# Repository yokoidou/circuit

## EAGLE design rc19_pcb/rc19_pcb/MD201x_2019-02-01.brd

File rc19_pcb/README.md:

rc19_pcb.zipには，3組の回路図・基板データファイル，合計6つのファイルが含まれます．
MD201x_2018-11-25.sch/brdは1次審査まで使用したモータドライバで，ファームウェアはここ(https://github.com/yskhara/md201x) に置いてあります．
MD201x_2019-02-01.sch/brdは1次審査以降に使用したモータドライバで，ファームウェアはここ(https://github.com/yskhara/mdpos201x) に置いてあります．
usbcan_20190426.sch/brdは2次落ち以降に発注したUSB-CAN基板です．ファームウェアはまだありませんし，基板もテストできていませんが，参考程度に添付しておきます．

Follow me on:
GitHub: https://github.com/yskhara

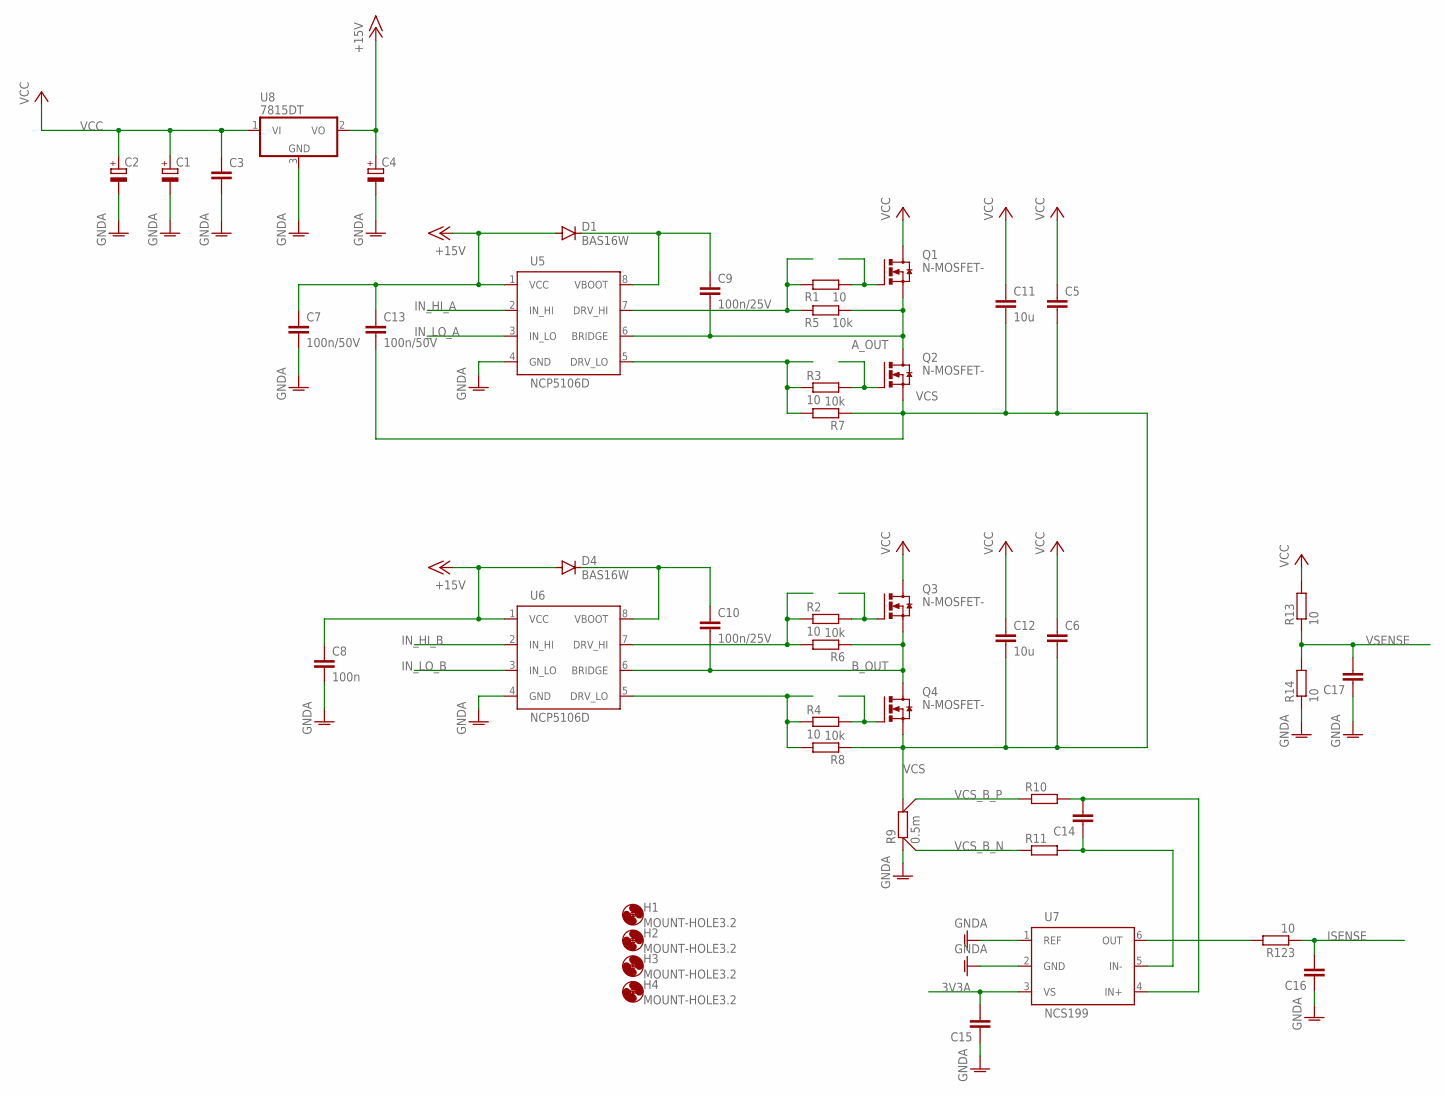
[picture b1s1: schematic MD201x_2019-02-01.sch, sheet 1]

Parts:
C1, C2: CPOL-EUE5-10.5; E5-10,5
C3, C5, C6, C14, C15, C16, C17: C-EUC0603; C0603
C4: CPOL-EUE2.5-5; E2,5-5
C7, C13: 100n/50V; C0603
C8: 100n; C0603
C9, C10: 100n/25V; C0603
C11, C12: 10u; C1210
D1, D4: BAS16W; SOD323-R
H1, H2, H3, H4: MOUNT-HOLE3.2; 3,2
Q1, Q2, Q3, Q4: N-MOSFET-; SOT669
R1, R2, R3, R4, R13, R14, R123: 10; R0603
R5, R6, R7, R8: 10k; R0603
R9: 0.5m; CSS2H-2512
R10, R11: R-EU_R0603; R0603
U5, U6: NCP5106D; SOIC127P600X175-8
U7: NCS199; SOT65P210X110-6
U8: 7815DT; TO252

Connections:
3V3A: C15.2, U7.3 (VS); also elsewhere on the board
+15V: C4.+, C7.1, C8.1, C13.1, D1.A, D4.A, U5.1 (VCC), U6.1 (VCC), U8.2 (VO); also elsewhere on the board
A_OUT: C9.2, Q1.1 (SOURCE), Q1.2 (SOURCE), Q1.3 (SOURCE), Q2.5 (DRAIN), R5.1, U5.6 (BRIDGE)
B_OUT: C10.2, Q3.1 (SOURCE), Q3.2 (SOURCE), Q3.3 (SOURCE), Q4.5 (DRAIN), R6.1, U6.6 (BRIDGE)
GNDA: C1.-, C2.-, C3.2, C4.-, C7.2, C8.2, C15.1, C16.1, C17.1, R9.1$1 (1), R9.1$2 (1), R14.1, U5.4 (GND), U6.4 (GND), U7.1 (REF), U7.2 (GND), U8.3 (GND); also elsewhere on the board
IN_HI_A: U5.2 (IN_HI); also elsewhere on the board
IN_HI_B: U6.2 (IN_HI); also elsewhere on the board
IN_LO_A: U5.3 (IN_LO); also elsewhere on the board
IN_LO_B: U6.3 (IN_LO); also elsewhere on the board
ISENSE: C16.2, R123.1; also elsewhere on the board
unnamed: R1.1, R5.2, U5.7 (DRV_HI)
unnamed: R2.1, R6.2, U6.7 (DRV_HI)
unnamed: Q1.4 (GATE), R1.2
unnamed: R4.1, R8.2, U6.5 (DRV_LO)
unnamed: R123.2, U7.6 (OUT)
unnamed: R3.1, R7.2, U5.5 (DRV_LO)
unnamed: Q3.4 (GATE), R2.2
unnamed: C14.2, R10.2, U7.4 (IN+)
unnamed: C14.1, R11.2, U7.5 (IN-)
unnamed: Q2.4 (GATE), R3.2
unnamed: Q4.4 (GATE), R4.2
unnamed: C10.1, D4.C, U6.8 (VBOOT)
unnamed: C9.1, D1.C, U5.8 (VBOOT)
VCC: C1.+, C2.+, C3.1, C5.1, C6.1, C11.1, C12.1, Q1.5 (DRAIN), Q3.5 (DRAIN), R13.2, U8.1 (VI)
VCS: C5.2, C6.2, C11.2, C12.2, C13.2, Q2.1 (SOURCE), Q2.2 (SOURCE), Q2.3 (SOURCE), Q4.1 (SOURCE), Q4.2 (SOURCE), Q4.3 (SOURCE), R7.1, R8.1, R9.2$1 (2), R9.2$2 (2)
VCS_B_N: R9.1S, R11.1
VCS_B_P: R9.2S, R10.1
VSENSE: C17.2, R13.1, R14.2; also elsewhere on the board

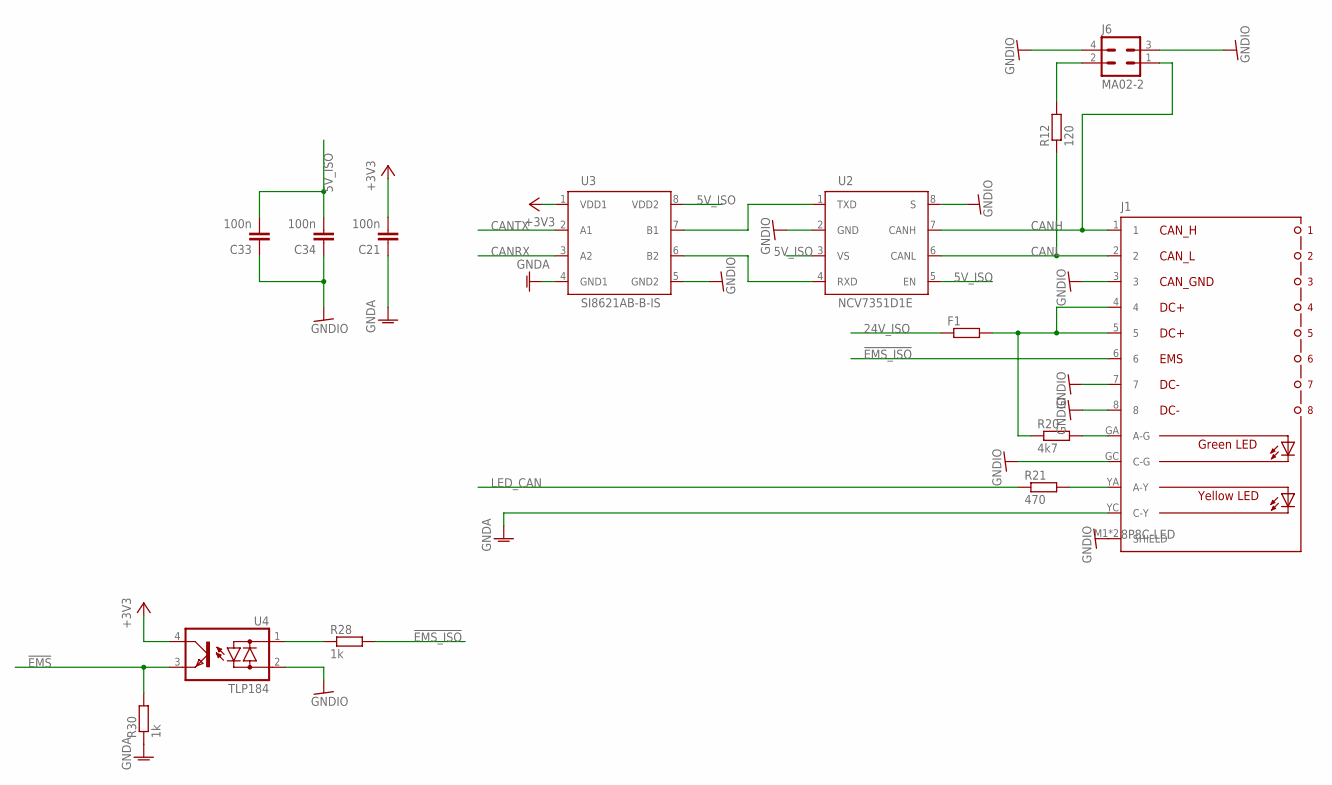
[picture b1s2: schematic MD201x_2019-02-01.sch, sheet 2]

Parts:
C21, C34: 100n; C0603
C33: 100n; C0805
F1: R-EU_R1206; R1206
J1: 8P8C-LED
J6: MA02-2; MA02-2W
R12: 120; R0603
R20: 4k7; R0603
R21: 470; R0603
R28, R30: 1k; R0603
U2: NCV7351D1E; SO08
U3: SI8621AB-B-IS; SO08
U4: TLP184; 11-4M1S

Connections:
5V_ISO: C33.2, C34.2, U2.3 (VS), U2.5 (EN), U3.8 (VDD2); also elsewhere on the board
24V_ISO: F1.1; also elsewhere on the board
!EMS: R30.2, U4.3 (E); also elsewhere on the board
!EMS_ISO: J1.6, R28.2
+3V3: C21.2, U3.1 (VDD1), U4.4 (C); also elsewhere on the board
CANH: J1.1, J6.1, U2.7 (CANH)
CANL: J1.2, R12.1, U2.6 (CANL)
CANRX: U3.3 (A2); also elsewhere on the board
CANTX: U3.2 (A1); also elsewhere on the board
GNDA: C21.1, J1.YC (C-Y), R30.1, U3.4 (GND1); also elsewhere on the board
GNDIO: C33.1, C34.1, J1.3, J1.7, J1.8, J1.GC (C-G), J1.M1 (SHIELD), J1.M2 (SHIELD), J6.3, J6.4, U2.2 (GND), U2.8 (S), U3.5 (GND2), U4.2 (AC2); also elsewhere on the board
LED_CAN: R21.1; also elsewhere on the board
unnamed: F1.2, J1.4, J1.5, R20.1
unnamed: J6.2, R12.2
unnamed: J1.GA (A-G), R20.2
unnamed: J1.YA (A-Y), R21.2
unnamed: U2.1 (TXD), U3.7 (B1)
unnamed: U2.4 (RXD), U3.6 (B2)
unnamed: R28.1, U4.1 (AC1)

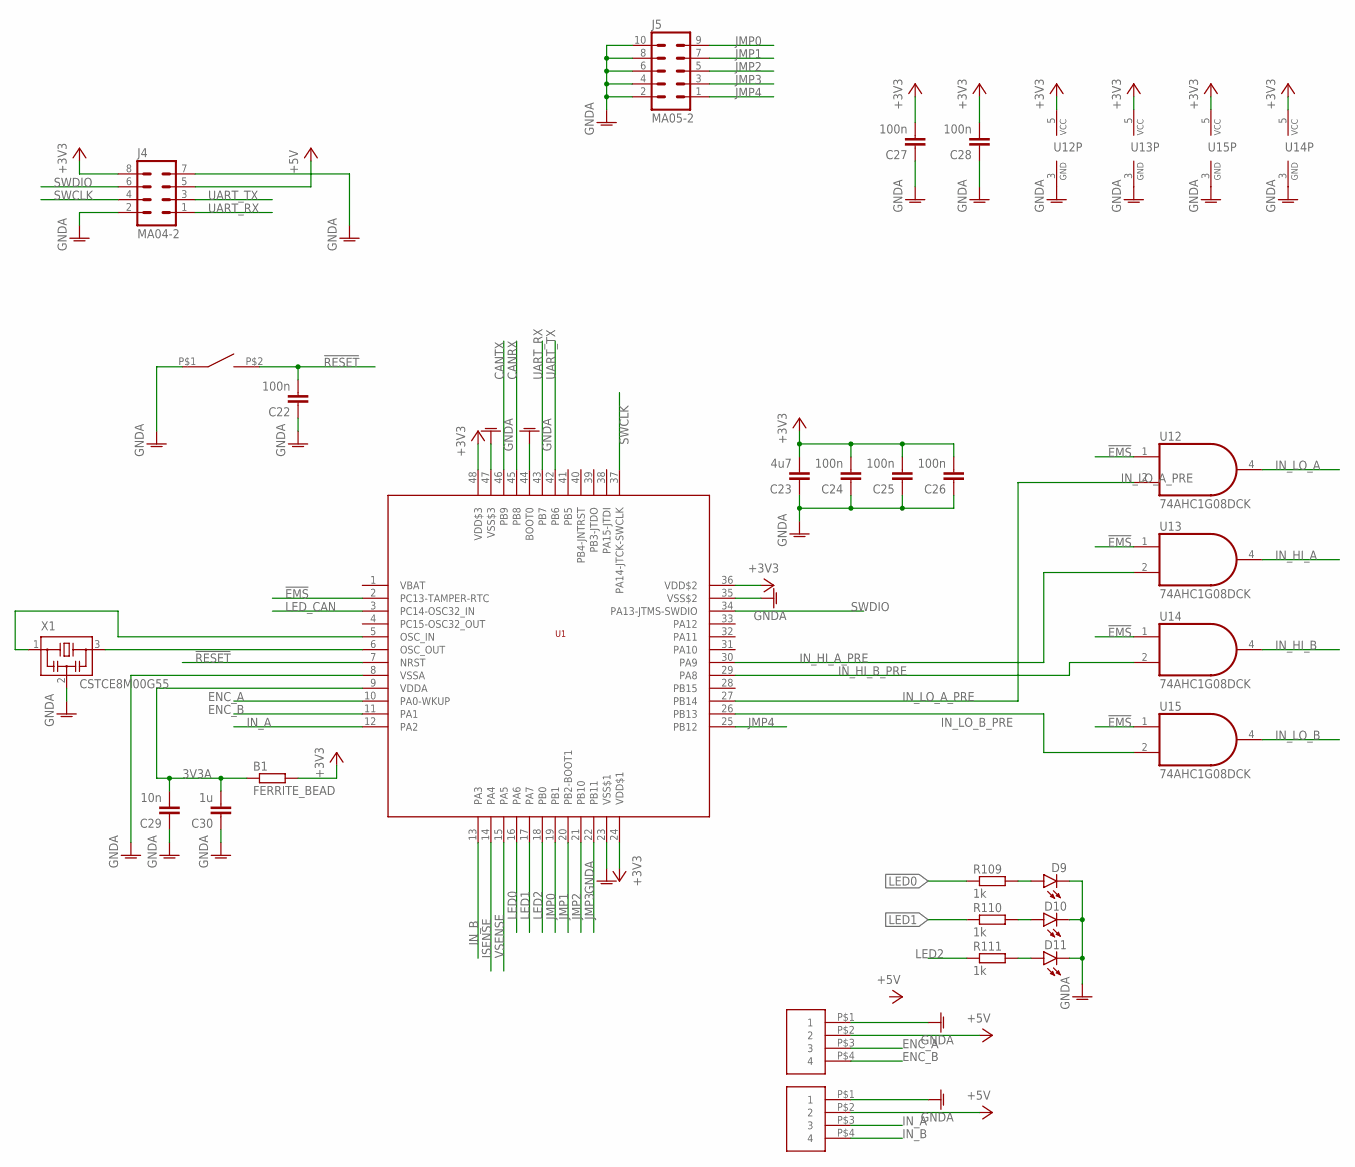
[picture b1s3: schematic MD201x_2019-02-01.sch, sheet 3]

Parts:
B1: FERRITE_BEAD; R0603
C22, C24, C25, C26, C27, C28: 100n; C0603
C23: 4u7; C0805
C29: 10n; C0603
C30: 1u; C0603
D9, D10, D11: LEDCHIPLED_0805; CHIPLED_0805
J2, J3: XH-4-SIDE; CON-XH-4-SIDE
J4: MA04-2; MA04-2W
J5: MA05-2; MA05-2W
R109, R110, R111: 1k; R0603
S1: SWITCH_TACTILETOP; SWITCH_TACTILE_3X6
U1: STM32F103C8; LQFP48
U12, U13, U14, U15: 74AHC1G08DCK; SC70-5
X1: CSTCE8M00G55

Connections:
3V3A: B1.1, C29.2, C30.2, U1.9 (VDDA); also elsewhere on the board
!EMS: U1.2 (PC13-TAMPER-RTC), U12.1 (I0), U13.1 (I0), U14.1 (I0), U15.1 (I0); also elsewhere on the board
!RESET: C22.2, S1.P$2 (2), U1.7 (NRST)
+3V3: B1.2, C23.2, C24.2, C25.2, C26.2, C27.2, C28.2, J4.8, U1.24 (VDD$1), U1.36 (VDD$2), U1.48 (VDD$3), U12.5 (VCC), U13.5 (VCC), U14.5 (VCC), U15.5 (VCC); also elsewhere on the board
+5V: J2.P$2 (2), J3.P$2 (2), J4.5; also elsewhere on the board
CANRX: U1.45 (PB8); also elsewhere on the board
CANTX: U1.46 (PB9); also elsewhere on the board
ENC_A: J2.P$3 (3), U1.10 (PA0-WKUP)
ENC_B: J2.P$4 (4), U1.11 (PA1)
GNDA: C22.1, C23.1, C24.1, C25.1, C26.1, C27.1, C28.1, C29.1, C30.1, D9.C, D10.C, D11.C, J2.P$1 (1), J3.P$1 (1), J4.2, J4.7, J5.2, J5.4, J5.6, J5.8, J5.10, S1.P$1 (1), U1.8 (VSSA), U1.23 (VSS$1), U1.35 (VSS$2), U1.44 (BOOT0), U1.47 (VSS$3), U12.3 (GND), U13.3 (GND), U14.3 (GND), U15.3 (GND), X1.2; also elsewhere on the board
IN_A: J3.P$3 (3), U1.12 (PA2)
IN_B: J3.P$4 (4), U1.13 (PA3)
IN_HI_A: U13.4 (O); also elsewhere on the board
IN_HI_A_PRE: U1.30 (PA9), U13.2 (I1)
IN_HI_B: U14.4 (O); also elsewhere on the board
IN_HI_B_PRE: U1.29 (PA8), U14.2 (I1)
IN_LO_A: U12.4 (O); also elsewhere on the board
IN_LO_A_PRE: U1.27 (PB14), U12.2 (I1)
IN_LO_B: U15.4 (O); also elsewhere on the board
IN_LO_B_PRE: U1.26 (PB13), U15.2 (I1)
ISENSE: U1.14 (PA4); also elsewhere on the board
JMP0: J5.9, U1.19 (PB1)
JMP1: J5.7, U1.20 (PB2-BOOT1)
JMP2: J5.5, U1.21 (PB10)
JMP3: J5.3, U1.22 (PB11)
JMP4: J5.1, U1.25 (PB12)
LED0: R109.1, U1.16 (PA6)
LED1: R110.1, U1.17 (PA7)
LED2: R111.1, U1.18 (PB0)
LED_CAN: U1.3 (PC14-OSC32_IN); also elsewhere on the board
unnamed: D10.A, R110.2
unnamed: D9.A, R109.2
unnamed: U1.6 (OSC_OUT), X1.3
unnamed: U1.5 (OSC_IN), X1.1
unnamed: D11.A, R111.2
SWCLK: J4.4, U1.37 (PA14-JTCK-SWCLK)
SWDIO: J4.6, U1.34 (PA13-JTMS-SWDIO)
UART_RX: J4.1, U1.43 (PB7)
UART_TX: J4.3, U1.42 (PB6)
VSENSE: U1.15 (PA5); also elsewhere on the board

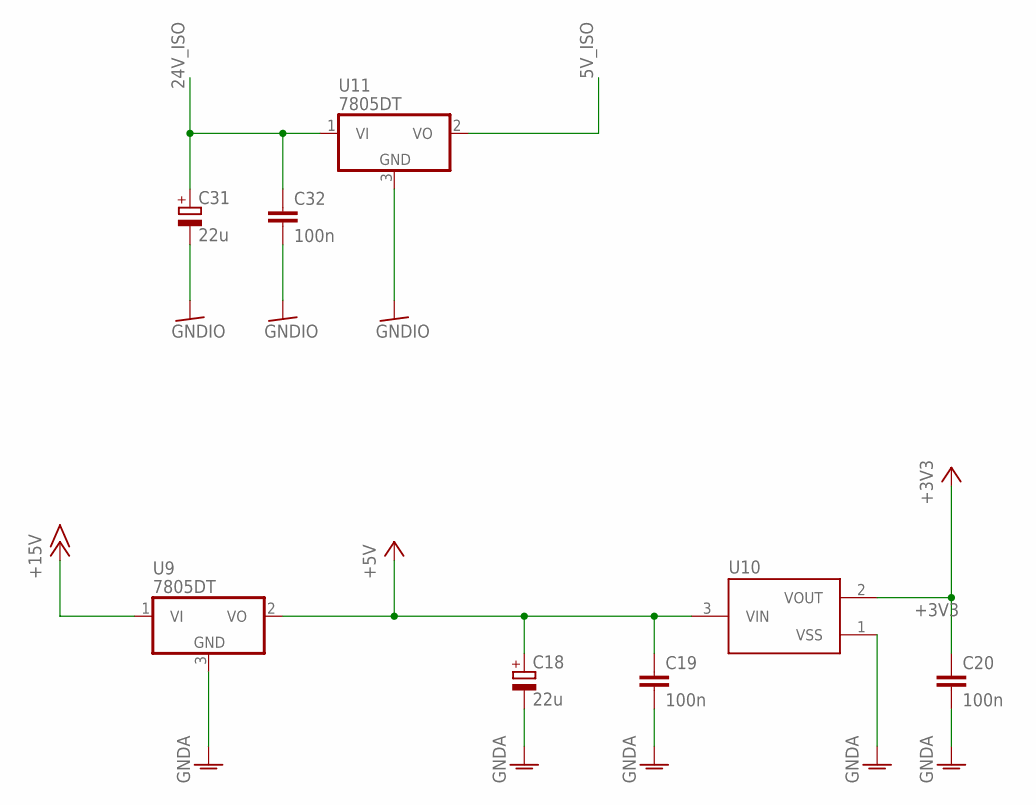
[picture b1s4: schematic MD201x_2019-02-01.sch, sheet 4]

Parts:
C18, C31: 22u; E2,5-5
C19, C20, C32: 100n; C0603
U9, U11: 7805DT; TO252
U10: XC6206; SOT95P240X110-3

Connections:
5V_ISO: U11.2 (VO); also elsewhere on the board
24V_ISO: C31.+, C32.1, U11.1 (VI); also elsewhere on the board
+3V3: C20.1, U10.2 (VOUT); also elsewhere on the board
+5V: C18.+, C19.1, U9.2 (VO), U10.3 (VIN); also elsewhere on the board
+15V: U9.1 (VI); also elsewhere on the board
GNDA: C18.-, C19.2, C20.2, U9.3 (GND), U10.1 (VSS); also elsewhere on the board
GNDIO: C31.-, C32.2, U11.3 (GND); also elsewhere on the board

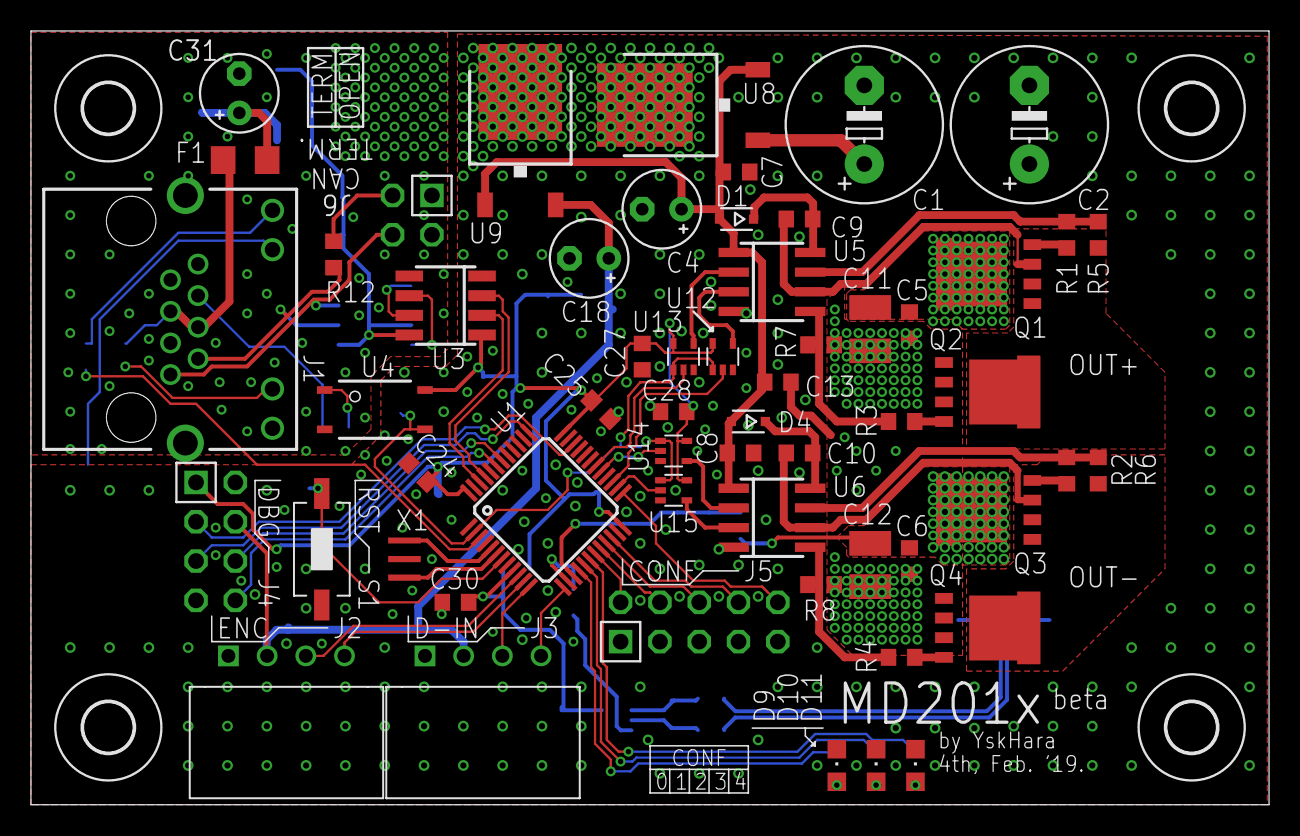
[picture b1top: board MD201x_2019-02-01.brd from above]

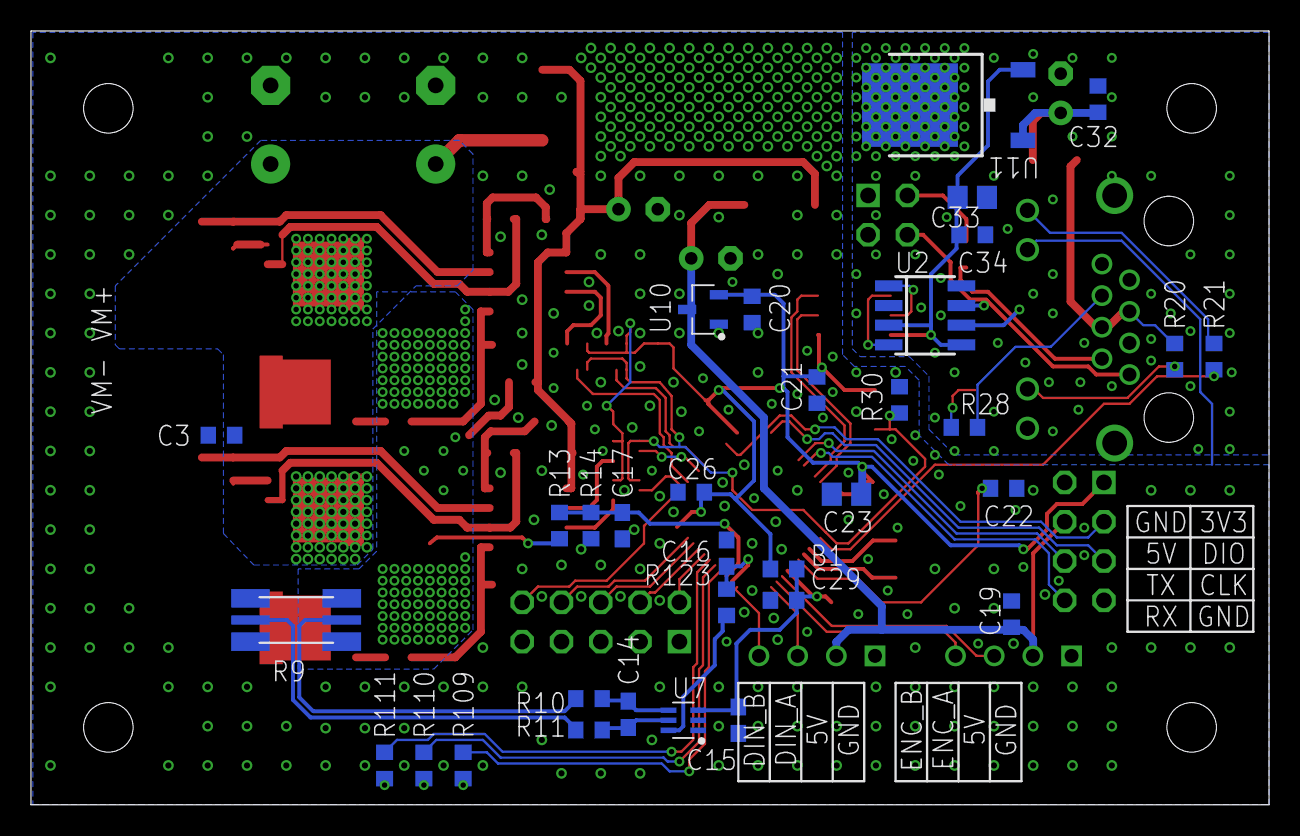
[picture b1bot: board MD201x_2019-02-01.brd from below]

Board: 2 copper layers, 80.0 x 50.0 mm, 94 parts (33 on the bottom side), 73 nets.

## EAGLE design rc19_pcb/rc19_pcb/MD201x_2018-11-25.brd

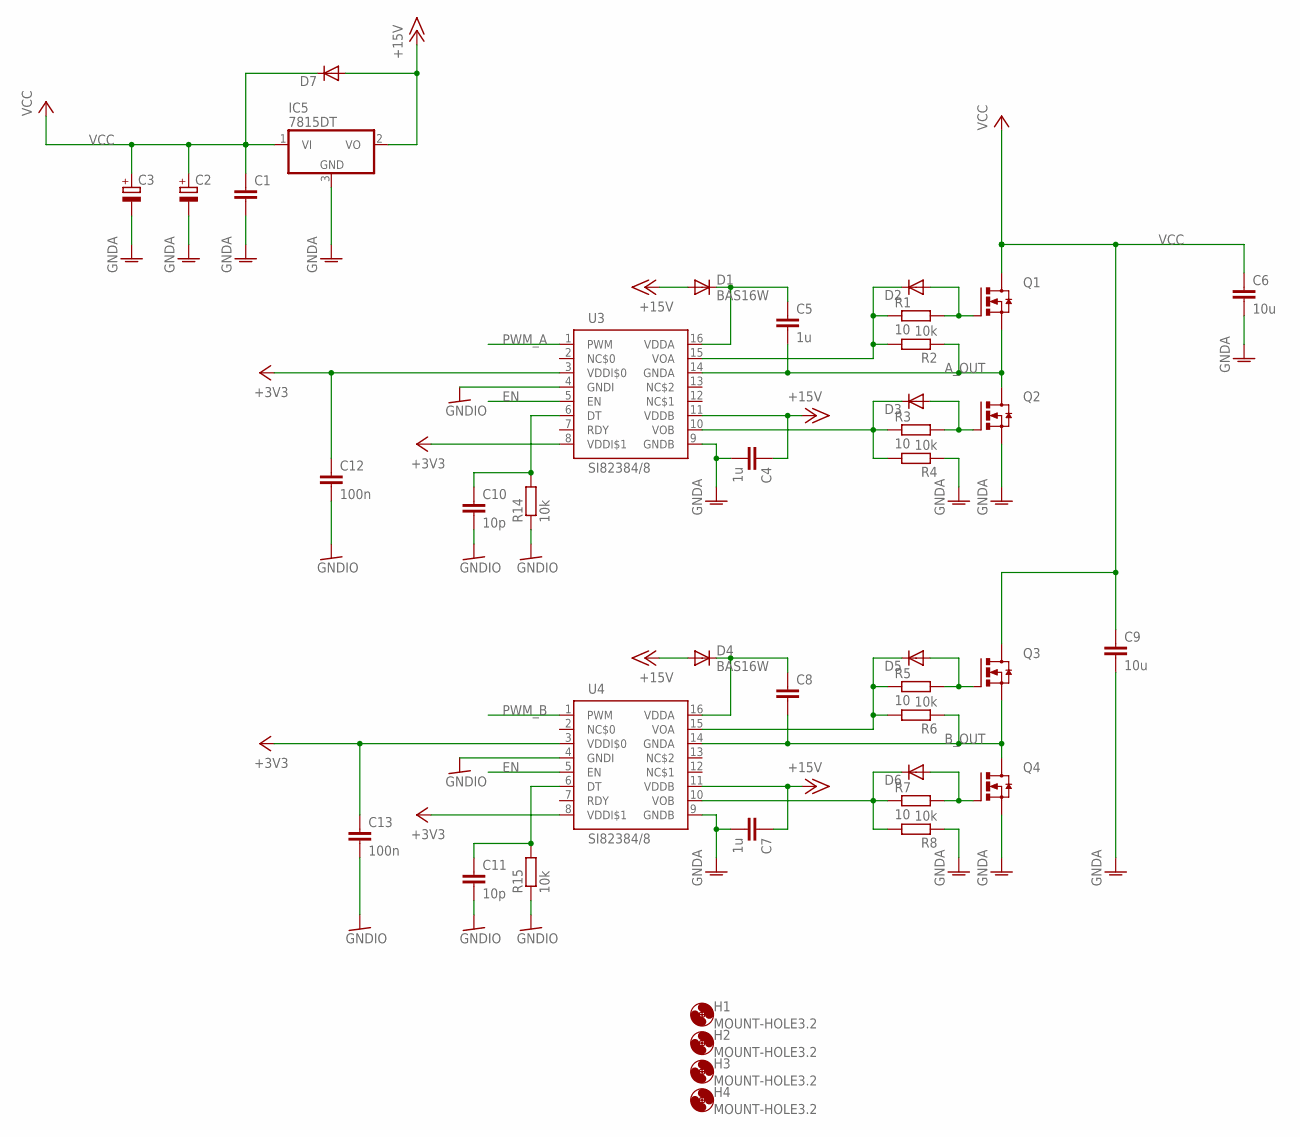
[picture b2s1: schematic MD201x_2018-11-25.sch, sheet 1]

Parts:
C1, C8: C-EUC0805; C0805
C2, C3: CPOL-EUE3.5-8; E3,5-8
C4, C5, C7: 1u; C0805
C6, C9: 10u; C1210
C10, C11: 10p; C0603
C12, C13: 100n; C0603
D1, D4: BAS16W; SOD323-R
D2, D3, D5, D6: DIODE-SOD523; SOD523
D7: DIODE-SOD323-R; SOD323-R
H1, H2, H3, H4: MOUNT-HOLE3.2; 3,2
IC5: 7815DT; TO252
Q1, Q2, Q3, Q4: -N_MOSFET-SOT669; SOT669
R1, R3, R5, R7: 10; R0603
R2, R4, R6, R8, R14, R15: 10k; R0603
U3, U4: SI82384/8; SOIC16

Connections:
+3V3: C12.1, C13.1, U3.3 (VDDI$0), U3.8 (VDDI$1), U4.3 (VDDI$0), U4.8 (VDDI$1); also elsewhere on the board
+15V: C4.1, C7.1, D1.A, D4.A, D7.A, IC5.2 (VO), U3.11 (VDDB), U4.11 (VDDB)
A_OUT: C5.2, Q1.1 (SOURCE), Q1.2 (SOURCE), Q1.3 (SOURCE), Q2.5 (DRAIN), R2.1, U3.14 (GNDA)
B_OUT: C8.2, Q3.1 (SOURCE), Q3.2 (SOURCE), Q3.3 (SOURCE), Q4.5 (DRAIN), R6.1, U4.14 (GNDA)
EN: U3.5 (EN), U4.5 (EN); also elsewhere on the board
GNDA: C1.2, C2.-, C3.-, C4.2, C6.2, C7.2, C9.2, IC5.3 (GND), Q2.1 (SOURCE), Q2.2 (SOURCE), Q2.3 (SOURCE), Q4.1 (SOURCE), Q4.2 (SOURCE), Q4.3 (SOURCE), R4.1, R8.1, U3.9 (GNDB), U4.9 (GNDB)
GNDIO: C10.2, C11.2, C12.2, C13.2, R14.1, R15.1, U3.4 (GNDI), U4.4 (GNDI); also elsewhere on the board
unnamed: D2.C, R1.1, R2.2, U3.15 (VOA)
unnamed: D5.C, R5.1, R6.2, U4.15 (VOA)
unnamed: D2.A, Q1.4 (GATE), R1.2
unnamed: D6.C, R7.1, R8.2, U4.10 (VOB)
unnamed: C10.1, R14.2, U3.6 (DT)
unnamed: C11.1, R15.2, U4.6 (DT)
unnamed: D3.C, R3.1, R4.2, U3.10 (VOB)
unnamed: D5.A, Q3.4 (GATE), R5.2
unnamed: D3.A, Q2.4 (GATE), R3.2
unnamed: D6.A, Q4.4 (GATE), R7.2
unnamed: C8.1, D4.C, U4.16 (VDDA)
unnamed: C5.1, D1.C, U3.16 (VDDA)
PWM_A: U3.1 (PWM); also elsewhere on the board
PWM_B: U4.1 (PWM); also elsewhere on the board
VCC: C1.1, C2.+, C3.+, C6.1, C9.1, D7.C, IC5.1 (VI), Q1.5 (DRAIN), Q3.5 (DRAIN)

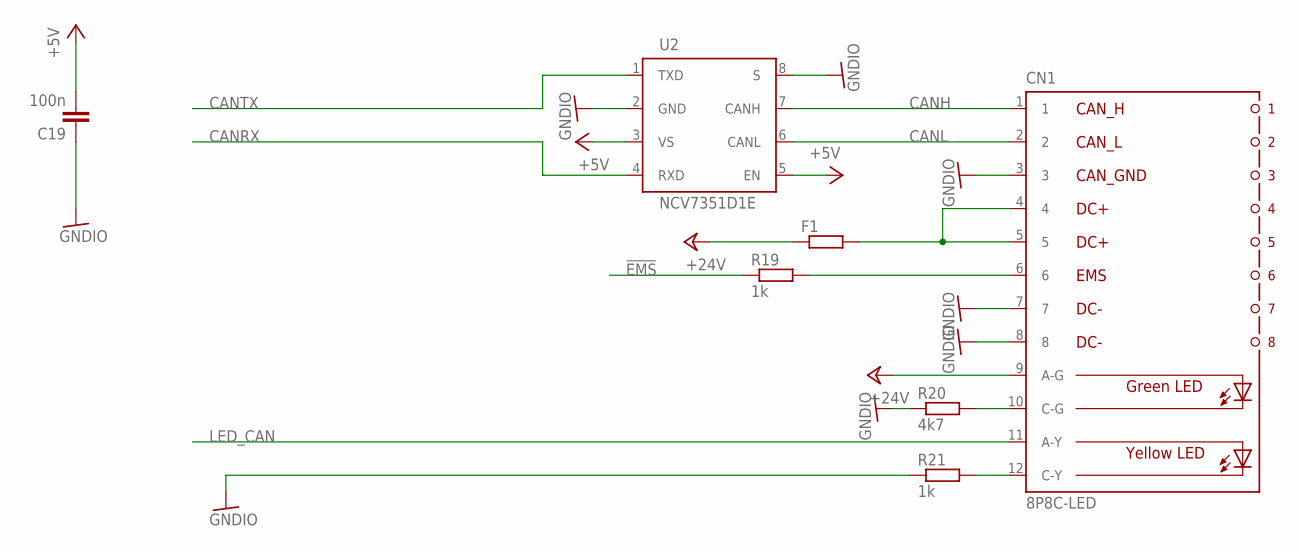
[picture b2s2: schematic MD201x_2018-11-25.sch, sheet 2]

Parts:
C19: 100n; C0603
CN1: 8P8C-LED
F1: R-EU_R1206; R1206
R19, R21: 1k; R0603
R20: 4k7; R0603
U2: NCV7351D1E; SO08

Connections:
!EMS: R19.1; also elsewhere on the board
!EMS_ISO: CN1.6, R19.2
+5V: C19.2, U2.3 (VS), U2.5 (EN); also elsewhere on the board
+24V: CN1.9 (A-G), F1.1; also elsewhere on the board
CANH: CN1.1, U2.7 (CANH)
CANL: CN1.2, U2.6 (CANL)
CANRX: U2.4 (RXD); also elsewhere on the board
CANTX: U2.1 (TXD); also elsewhere on the board
GNDIO: C19.1, CN1.3, CN1.7, CN1.8, R20.1, R21.1, U2.2 (GND), U2.8 (S); also elsewhere on the board
LED_CAN: CN1.11 (A-Y); also elsewhere on the board
unnamed: CN1.4, CN1.5, F1.2
unnamed: CN1.10 (C-G), R20.2
unnamed: CN1.12 (C-Y), R21.2

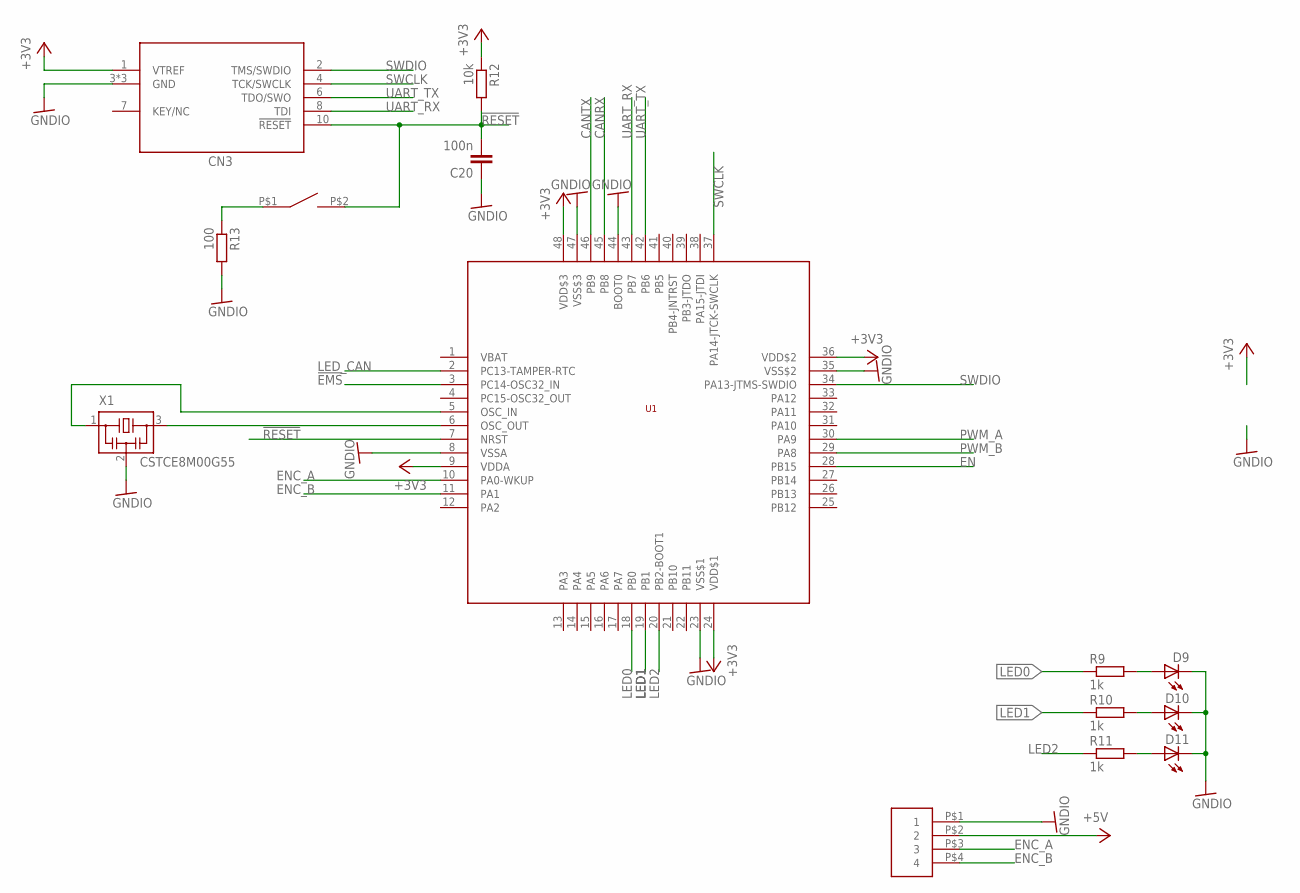
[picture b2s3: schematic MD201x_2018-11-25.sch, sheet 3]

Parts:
C20: 100n; C0603
CN2: XH-4-SIDE; CON-XH-4-SIDE
CN3: CON_SWD_1.27_SMD
D9, D10, D11: LEDCHIPLED_0805; CHIPLED_0805
R9, R10, R11: 1k; R0603
R12: 10k; R0603
R13: 100; R0603
SW1: SWITCH_TACTILETOP; SWITCH_TACTILE_3X6
U1: STM32F103C8; LQFP48
X1: CSTCE8M00G55

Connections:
!EMS: U1.3 (PC14-OSC32_IN); also elsewhere on the board
!RESET: C20.2, CN3.10 (!RESET), R12.2, SW1.P$2 (2), U1.7 (NRST)
+3V3: CN3.1 (VTREF), R12.1, U1.9 (VDDA), U1.24 (VDD$1), U1.36 (VDD$2), U1.48 (VDD$3); also elsewhere on the board
+5V: CN2.P$2 (2); also elsewhere on the board
CANRX: U1.45 (PB8); also elsewhere on the board
CANTX: U1.46 (PB9); also elsewhere on the board
EN: U1.28 (PB15); also elsewhere on the board
ENC_A: CN2.P$3 (3), U1.10 (PA0-WKUP)
ENC_B: CN2.P$4 (4), U1.11 (PA1)
GNDIO: C20.1, CN2.P$1 (1), CN3.3 (GND), CN3.5 (GND), CN3.9 (GND), D9.C, D10.C, D11.C, R13.2, U1.8 (VSSA), U1.23 (VSS$1), U1.35 (VSS$2), U1.44 (BOOT0), U1.47 (VSS$3), X1.2; also elsewhere on the board
LED0: R9.1, U1.18 (PB0)
LED1: R10.1, U1.19 (PB1)
LED2: R11.1, U1.20 (PB2-BOOT1)
LED_CAN: U1.2 (PC13-TAMPER-RTC); also elsewhere on the board
unnamed: D10.A, R10.2
unnamed: D9.A, R9.2
unnamed: U1.6 (OSC_OUT), X1.3
unnamed: R13.1, SW1.P$1 (1)
unnamed: U1.5 (OSC_IN), X1.1
unnamed: D11.A, R11.2
PWM_A: U1.30 (PA9); also elsewhere on the board
PWM_B: U1.29 (PA8); also elsewhere on the board
SWCLK: CN3.4 (TCK/SWCLK), U1.37 (PA14-JTCK-SWCLK)
SWDIO: CN3.2 (TMS/SWDIO), U1.34 (PA13-JTMS-SWDIO)
UART_RX: CN3.8 (TDI), U1.43 (PB7)
UART_TX: CN3.6 (TDO/SWO), U1.42 (PB6)

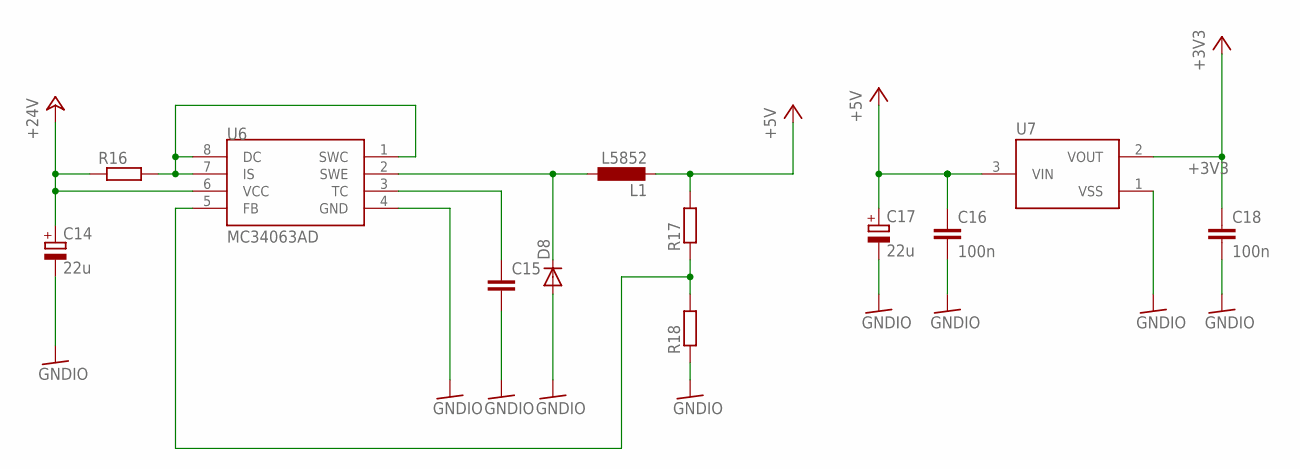
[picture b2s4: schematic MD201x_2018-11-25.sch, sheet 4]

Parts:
C14, C17: 22u; E2-5
C15: C-EUC0603; C0603
C16, C18: 100n; C0603
D8: DIODE-SOD123; SOD123
L1: L5852
R16: R-EU_R1206; R1206
R17, R18: R-EU_R0603; R0603
U6: MC34063AD; SOIC8
U7: XC6206; SOT95P240X110-3

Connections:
+3V3: C18.1, U7.2 (VOUT); also elsewhere on the board
+5V: C16.1, C17.+, L1.P$2 (2), R17.2, U7.3 (VIN); also elsewhere on the board
+24V: C14.+, R16.1, U6.6 (VCC); also elsewhere on the board
GNDIO: C14.-, C15.2, C16.2, C17.-, C18.2, D8.A, R18.1, U6.4 (GND), U7.1 (VSS); also elsewhere on the board
unnamed: R16.2, U6.1 (SWC), U6.7 (IS), U6.8 (DC)
unnamed: D8.C, L1.P$1 (1), U6.2 (SWE)
unnamed: C15.1, U6.3 (TC)
unnamed: R17.1, R18.2, U6.5 (FB)

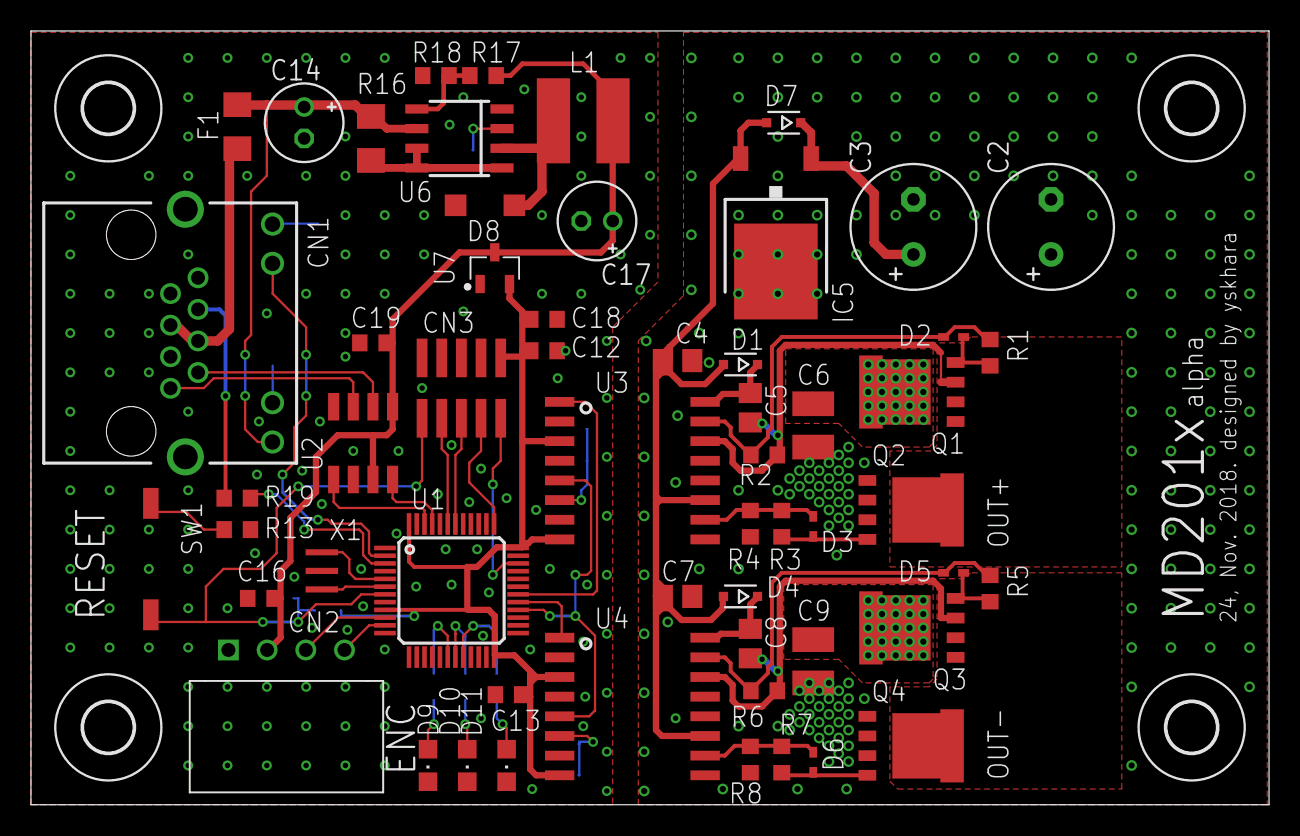
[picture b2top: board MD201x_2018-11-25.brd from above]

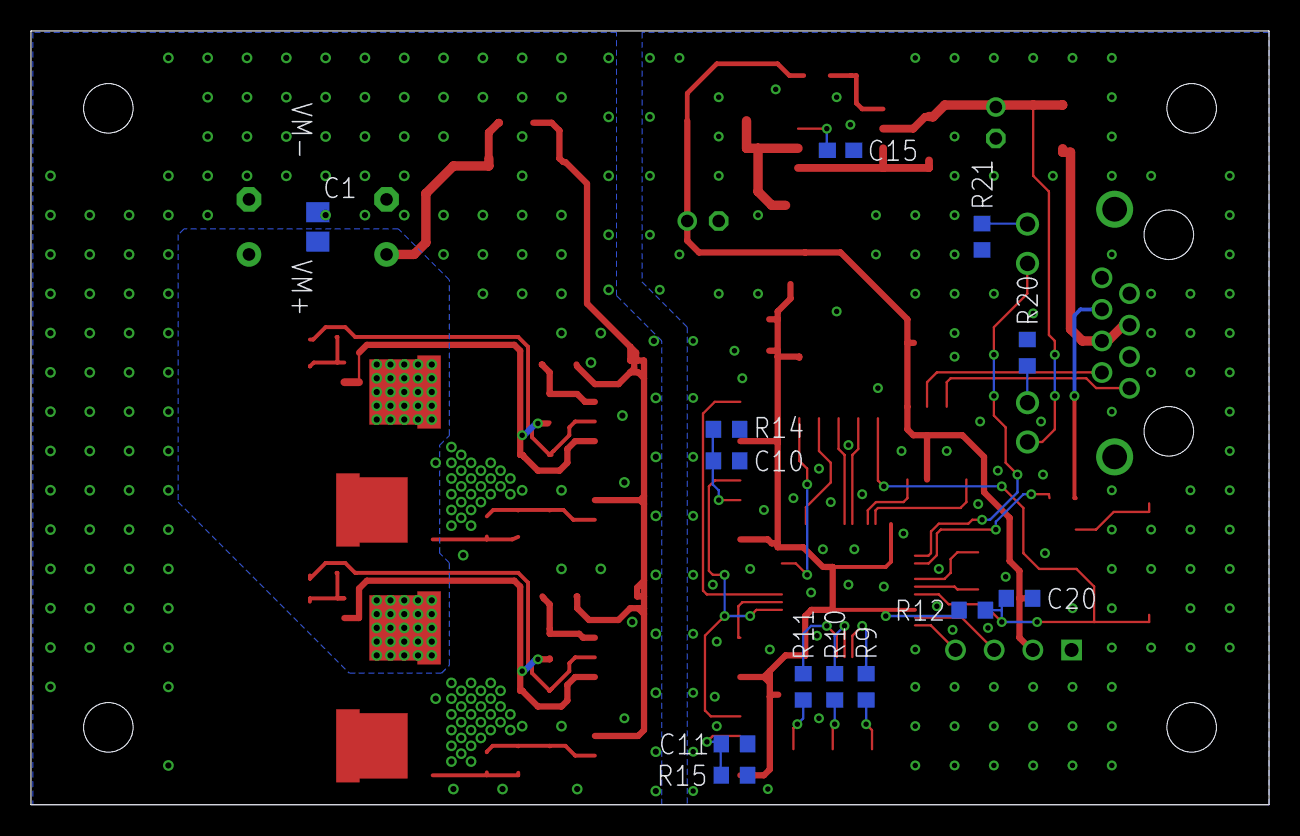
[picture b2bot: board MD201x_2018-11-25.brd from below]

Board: 2 copper layers, 80.0 x 50.0 mm, 74 parts (13 on the bottom side), 54 nets.

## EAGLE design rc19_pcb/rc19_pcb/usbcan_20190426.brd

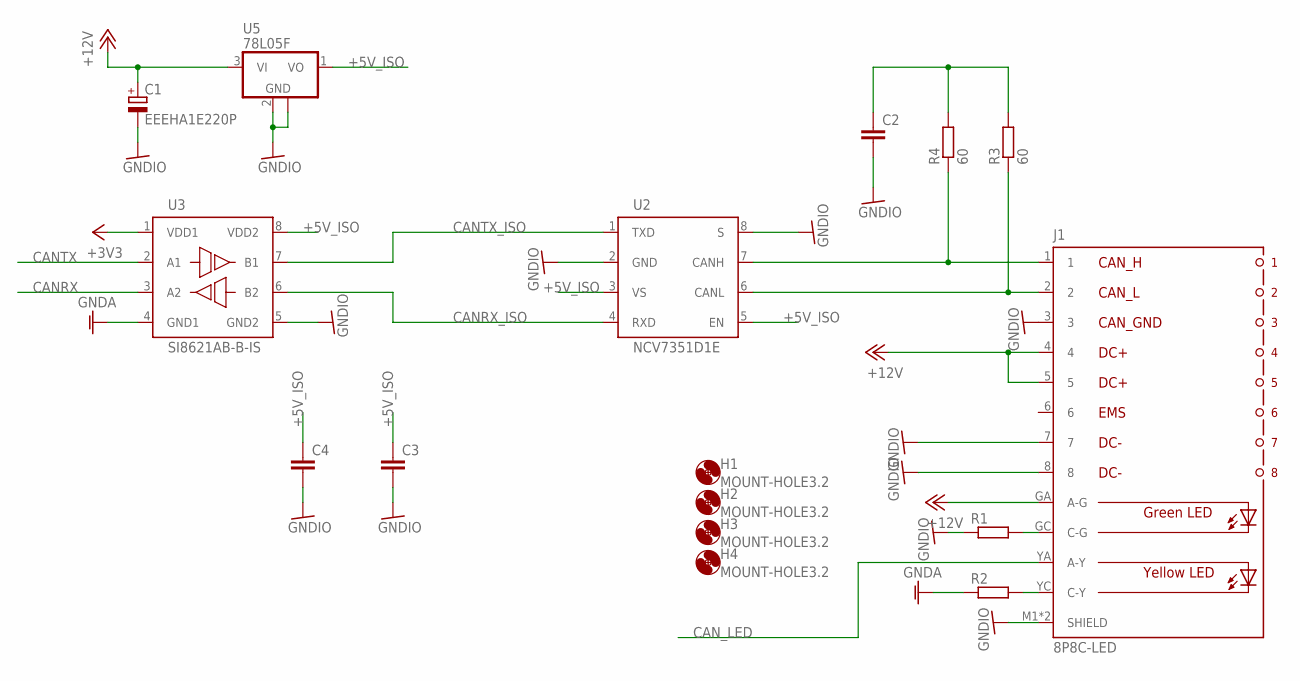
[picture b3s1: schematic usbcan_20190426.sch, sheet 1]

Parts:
C1: EEEHA1E220P; 153CLV-0605
C2, C3, C4: C-EUC0603; C0603
H1, H2, H3, H4: MOUNT-HOLE3.2; 3,2
J1: 8P8C-LED
R1, R2: R-EU_R0603; R0603
R3, R4: 60; R0603
U2: NCV7351D1E; SO08
U3: SI8621AB-B-IS; SO08
U5: 78L05F; SOT89

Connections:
+3V3: U3.1 (VDD1); also elsewhere on the board
+5V_ISO: C3.1, C4.1, U2.3 (VS), U2.5 (EN), U3.8 (VDD2), U5.1 (VO)
+12V: C1.+, J1.4, J1.5, J1.GA (A-G), U5.3 (VI)
CANH: J1.1, R4.1, U2.7 (CANH)
CANL: J1.2, R3.1, U2.6 (CANL)
CANRX: U3.3 (A2); also elsewhere on the board
CANRX_ISO: U2.4 (RXD), U3.6 (B2)
CANTX: U3.2 (A1); also elsewhere on the board
CANTX_ISO: U2.1 (TXD), U3.7 (B1)
CAN_LED: J1.YA (A-Y); also elsewhere on the board
GNDA: R2.1, U3.4 (GND1); also elsewhere on the board
GNDIO: C1.-, C2.2, C3.2, C4.2, J1.3, J1.7, J1.8, J1.M1 (SHIELD), J1.M2 (SHIELD), R1.1, U2.2 (GND), U2.8 (S), U3.5 (GND2), U5.2 (GND), U5.2@1 (GND)
unnamed: J1.GC (C-G), R1.2
unnamed: J1.YC (C-Y), R2.2
unnamed: C2.1, R3.2, R4.2

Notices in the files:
parts and their libraries:
con-molex-usb: (C) 2014 Tomasz Boleslaw CEDRO, cederom@tlen.pl, http://www.tomek.cedro.info.
